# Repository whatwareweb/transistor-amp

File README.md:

# transistor-amp
Simple transistor amplifier for Hack Club Solder 

This amplifier is based on the highly popular LM386 op-amp chip, although it has been somewhat downgraded for the sake of low component count (eg no constant current source, etc)

### Features
 - Class AB for higher efficiency
 - Runs on ~6V (2xCR2032 or external power supply input)
 - Small size, crammed in just over 3 square inches
 - Decent performance in SPICE simulation
   - higher THD than the original IC but not too bad
 - 250mW power output (yeah that's pretty low 😭)

### BOM
| Part                | Qty   | Notes                       |
| -------------       | ----- | ---                         |
| Battery holder 2032 | 2     |                             |
| 820uF Capacitor     | 1     |                             |
| Generic diode       | 2     | Needs to have 0.7v Vf       |
| 5mm terminal block  | 1     | Optional                    |
| NPN transistor      | 5     | I used 2N3904               |
| PNP transistor      | 4     | I used 2N3906               |
| 10k potentiometer   | 1     |                             |
| 10k resistor        | 2     |                             |
| 1.5k resistor       | 1     |                             |
| 15k resistor        | 1     |                             |
| 47k resistor        | 1     |                             |
| 220 ohm resistor    | 3     |                             |

### 3d view

### Schematic

### PCB

### Simulation results

slack username: `@whatware`

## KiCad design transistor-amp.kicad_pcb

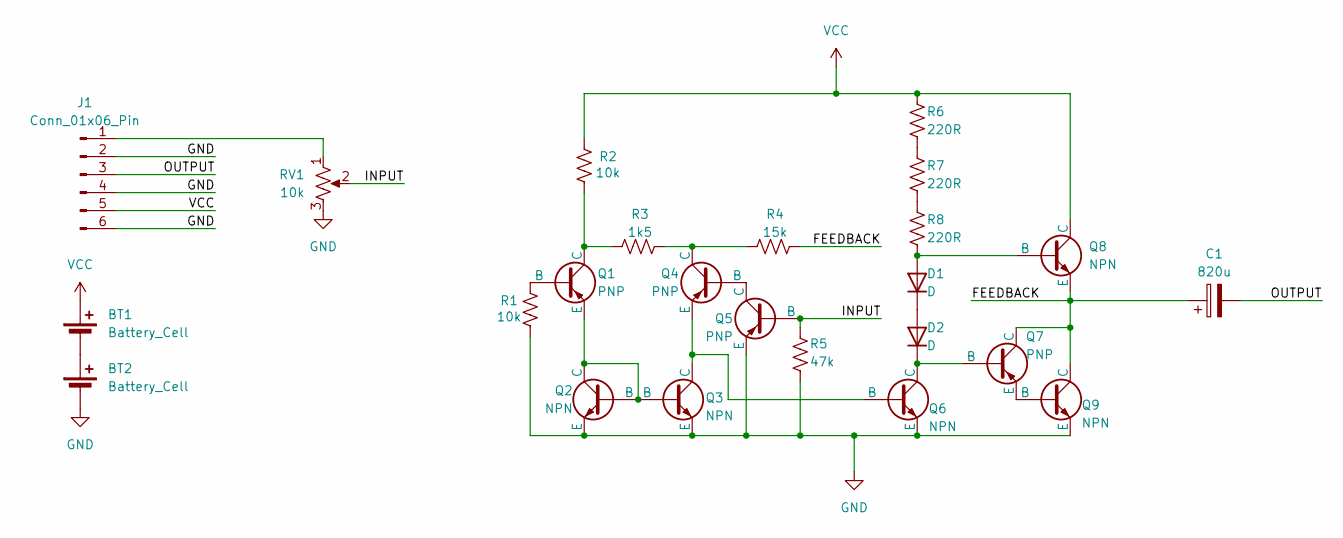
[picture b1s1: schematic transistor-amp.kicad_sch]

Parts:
BT1, BT2: Battery_Cell; BatteryHolder_Keystone_3034_1x20mm
C1: 820u; CP_Radial_D8.0mm_P3.50mm
D1, D2: D; D_DO-35_SOD27_P10.16mm_Horizontal
J1: Conn_01x06_Pin; TerminalBlock_bornier-6_P5.08mm
Q1, Q4, Q5, Q7: PNP; TO-92L_Inline
Q2, Q3, Q6, Q8, Q9: NPN; TO-92L_Inline
R1, R2: 10k; R_Axial_DIN0207_L6.3mm_D2.5mm_P7.62mm_Horizontal
R3: 1k5; R_Axial_DIN0207_L6.3mm_D2.5mm_P7.62mm_Horizontal
R4: 15k; R_Axial_DIN0207_L6.3mm_D2.5mm_P7.62mm_Horizontal
R5: 47k; R_Axial_DIN0207_L6.3mm_D2.5mm_P7.62mm_Horizontal
R6, R7, R8: 220R; R_Axial_DIN0207_L6.3mm_D2.5mm_P7.62mm_Horizontal
RV1: 10k; Potentiometer_Vishay_T73YP_Vertical

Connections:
/FEEDBACK: C1.1, Q7.1 (C), Q8.3 (E), Q9.1 (C), R4.2
/INPUT: Q5.2 (B), R5.1, RV1.2
/OUTPUT: C1.2, J1.3
GND: BT2.2 (-), J1.2, J1.4, J1.6, Q2.3 (E), Q3.3 (E), Q5.3 (E), Q6.3 (E), Q9.3 (E), R1.2, R5.2, RV1.3
unnamed: BT1.2 (-), BT2.1 (+)
unnamed: D1.2 (A), Q8.2 (B), R8.2
unnamed: D1.1 (K), D2.2 (A)
unnamed: D2.1 (K), Q6.1 (C), Q7.2 (B)
unnamed: J1.1, RV1.1
unnamed: Q1.2 (B), R1.1
unnamed: Q1.1 (C), R2.1, R3.1
unnamed: Q1.3 (E), Q2.1 (C), Q2.2 (B), Q3.2 (B)
unnamed: Q3.1 (C), Q4.3 (E), Q6.2 (B)
unnamed: Q4.2 (B), Q5.1 (C)
unnamed: Q4.1 (C), R3.2, R4.1
unnamed: Q7.3 (E), Q9.2 (B)
unnamed: R6.2, R7.1
unnamed: R7.2, R8.1
VCC: BT1.1 (+), J1.5, Q8.1 (C), R2.2, R6.1

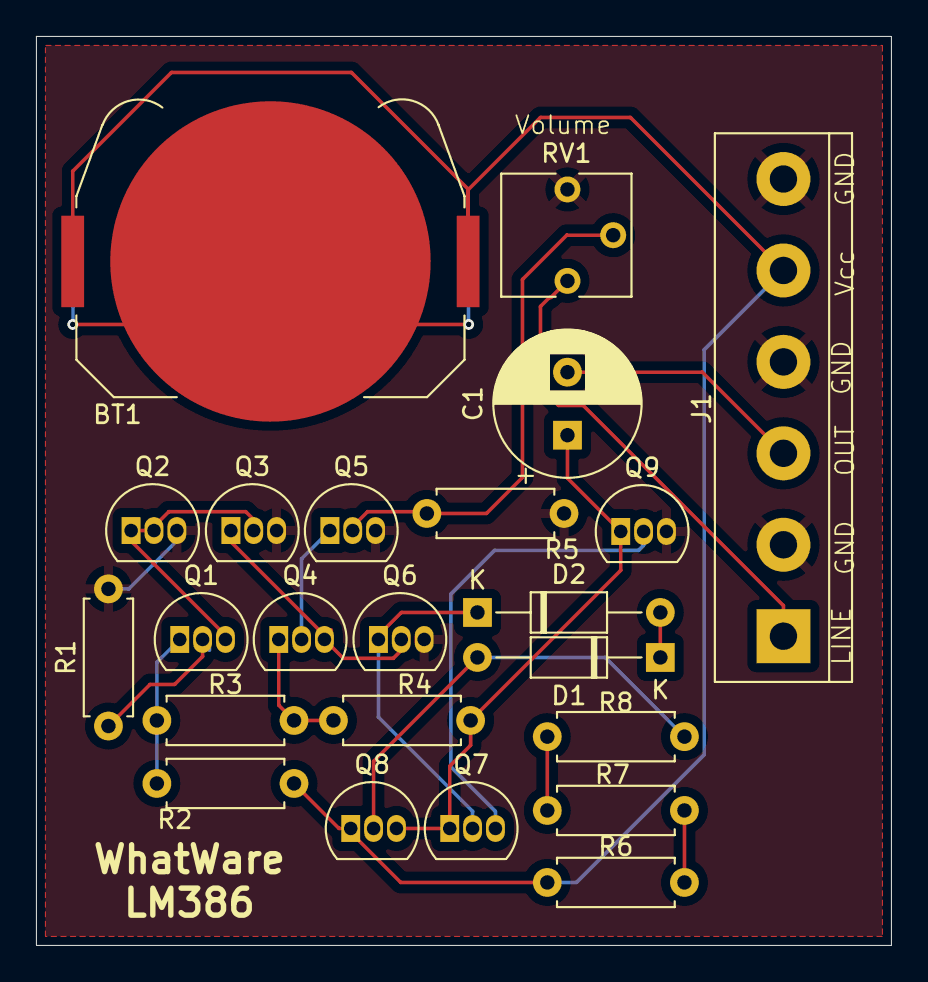
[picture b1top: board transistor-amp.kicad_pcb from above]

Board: 2 copper layers, 47.5 x 50.5 mm, 24 parts (1 on the bottom side), 19 nets.

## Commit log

2025-05-15 create kicad project
2025-05-30 finish schematic+pcb
2025-05-30 add gerber/drill files
